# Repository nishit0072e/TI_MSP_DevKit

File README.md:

### 3D View

### Schematic View

### Front Copper

### Rear Copper

### SilkScreen

### Solder Mask

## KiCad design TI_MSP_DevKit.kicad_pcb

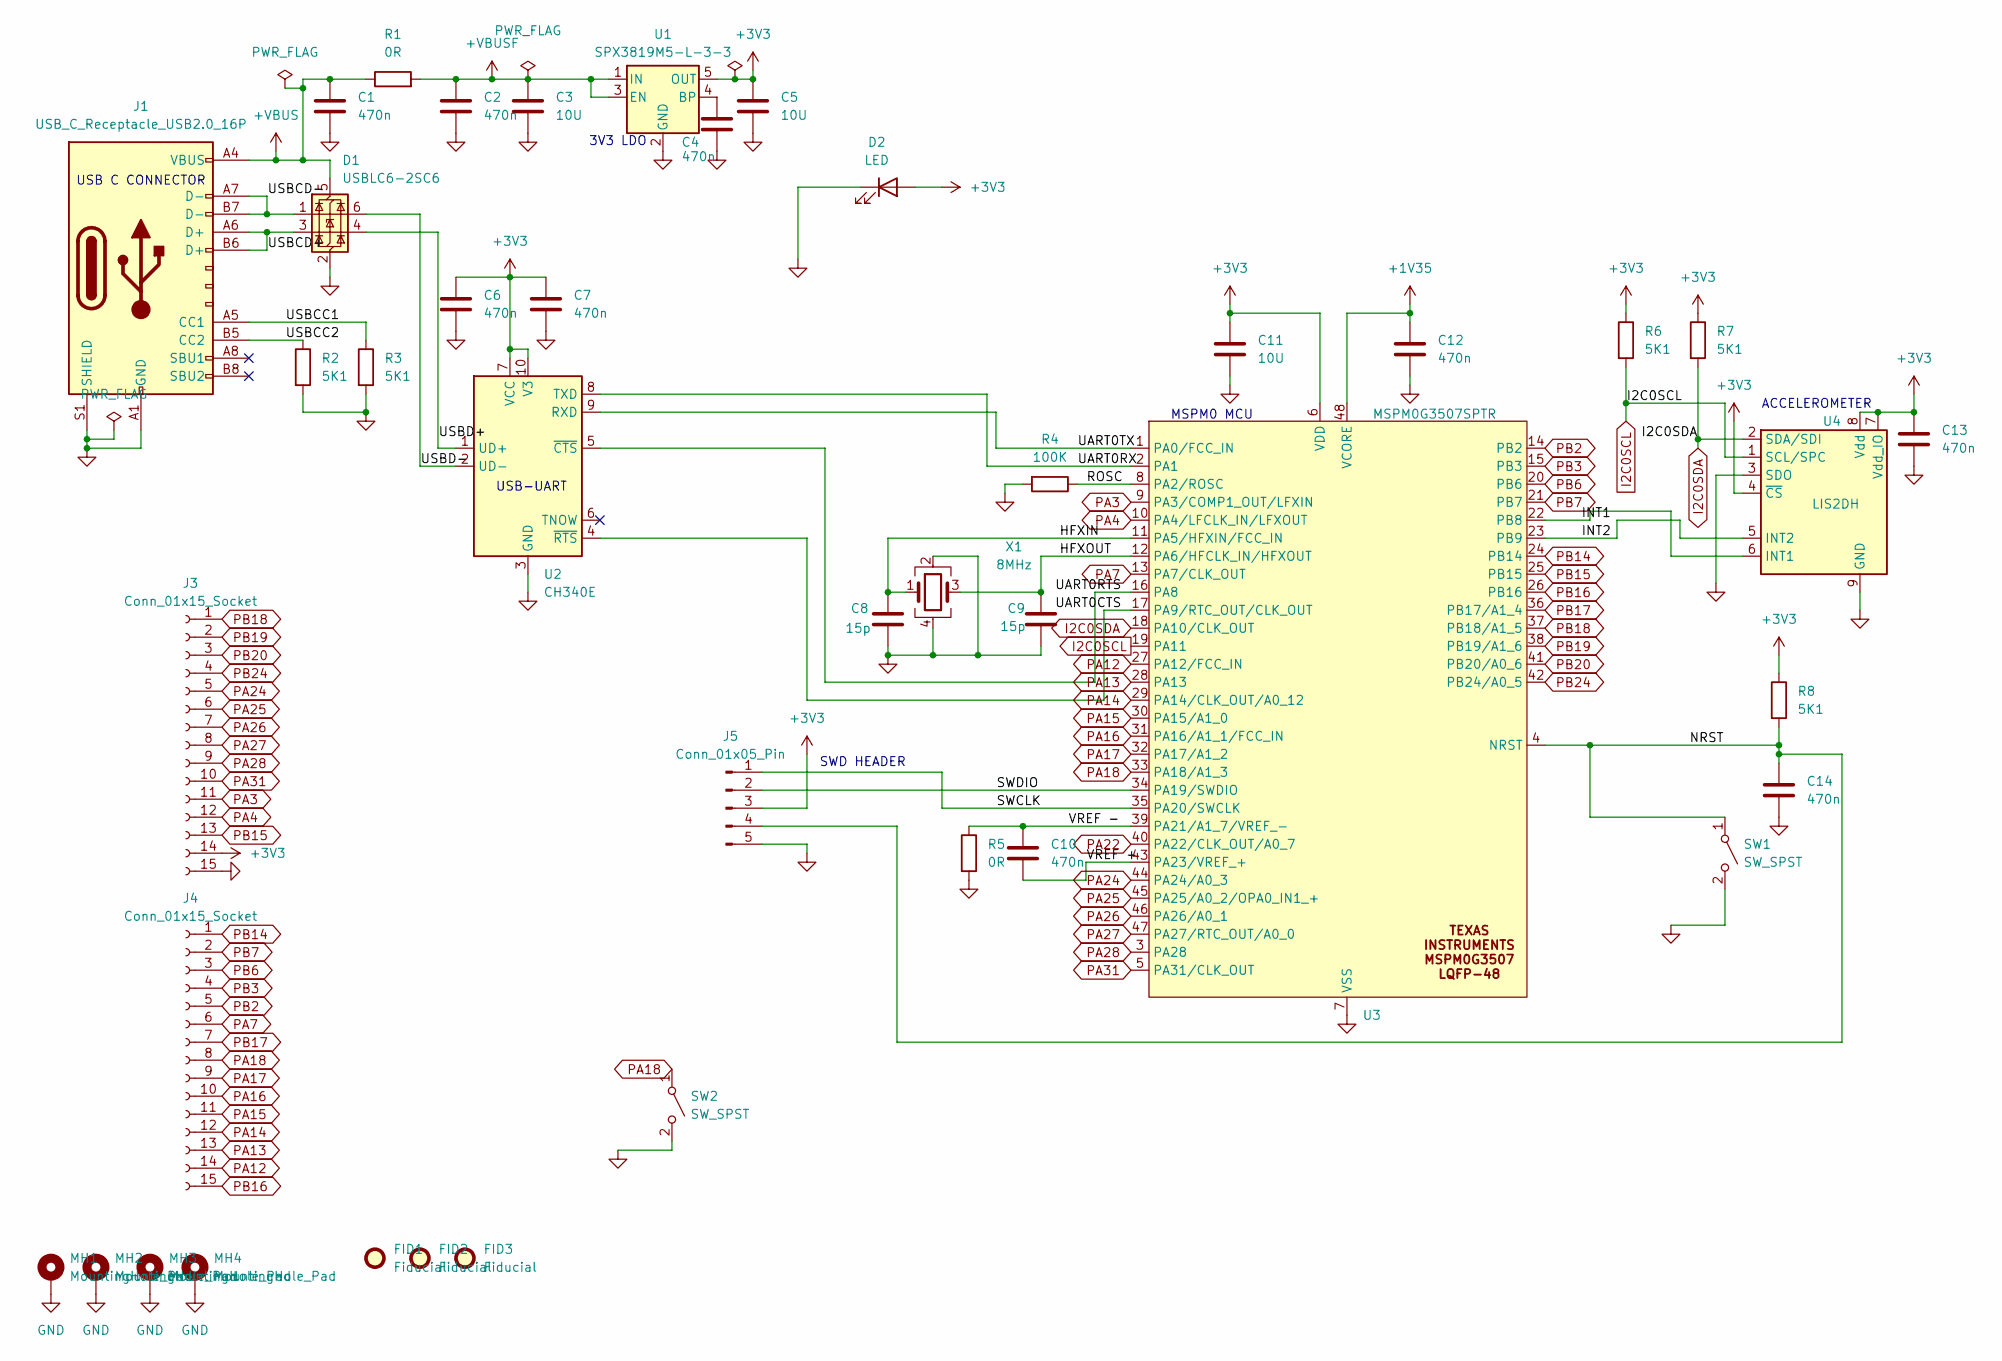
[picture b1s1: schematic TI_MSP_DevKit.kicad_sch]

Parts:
C1, C2, C4, C6, C7, C10, C12, C13, C14: 470n; C_0603_1608Metric_Pad1.08x0.95mm_HandSolder; Part Number CL21B474KBFNNNE; LCSC C13967
C3, C5, C11: 10U; C_0805_2012Metric_Pad1.18x1.45mm_HandSolder; Part Number CL21A106KAYNNNE; LCSC C15850
C8, C9: 15p; C_0603_1608Metric_Pad1.08x0.95mm_HandSolder; Part Number CL21B474KBFNNNE; LCSC C2594277
D1: USBLC6-2SC6; SOT-23-6; LCSC C2827654
D2: LED; LED_0603_1608Metric; LCSC C19171390
FID1, FID2, FID3: Fiducial; Fiducial_1mm_Mask2mm
J1: USB_C_Receptacle_USB2.0_16P; USB_C_Receptacle_GCT_USB4105-xx-A_16P_TopMnt_Horizontal; LCSC C2765186
J3, J4: Conn_01x15_Socket; PinSocket_1x15_P2.54mm_Vertical; LCSC C7499333
J5: Conn_01x05_Pin; PinSocket_1x05_P2.54mm_Vertical; LCSC C42431835
MH1, MH2, MH3, MH4: MountingHole_Pad; MountingHole_3.2mm_M3_Pad_Via
R1, R5: 0R; R_0603_1608Metric_Pad0.98x0.95mm_HandSolder; LCSC C95177
R2, R3, R6, R7, R8: 5K1; R_0603_1608Metric_Pad0.98x0.95mm_HandSolder; LCSC C2907044
R4: 100K; R_0603_1608Metric_Pad0.98x0.95mm_HandSolder; Part Number RT0603BRD07100KL; LCSC C122538
SW1, SW2: SW_SPST; SW_SPST_B3U-1000P; LCSC C720477
U1: SPX3819M5-L-3-3; SOT-23-5; LCSC C9055
U2: CH340E; MSOP-10_3x3mm_P0.5mm; LCSC C99652
U3: MSPM0G3507SPTR; LQFP-48_7x7mm_P0.5mm; Manufacturer Part Number MSPM0G3507SPTR; LCSC C22362630
U4: LIS2DH; LGA-14_2x2mm_P0.35mm_LayoutBorder3x4y; LCSC C110926
X1: 8MHz; Crystal_SMD_3225-4Pin_3.2x2.5mm_HandSoldering; LCSC C390495

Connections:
+1V35: C12.1, U3.48 (VCORE)
+3V3: C5.1, C6.1, C7.1, C11.1, C13.1, D2.2 (A), J3.14, J5.3, R6.1, R7.1, R8.1, U1.5 (OUT), U2.7 (VCC), U2.10 (V3), U3.6 (VDD), U4.4 (~CS), U4.7 (Vdd_IO), U4.8 (Vdd)
+VBUS: C1.1, D1.5 (VBUS), J1.A4 (VBUS), J1.A9 (VBUS), J1.B4 (VBUS), J1.B9 (VBUS), R1.1
+VBUSF: C2.1, C3.1, R1.2, U1.1 (IN), U1.3 (EN)
/HFXIN: C8.1, U3.11 (PA5/HFXIN/FCC_IN), X1.1
/HFXOUT: C9.1, U3.12 (PA6/HFCLK_IN/HFXOUT), X1.3
/INT1: U3.22 (PB8), U4.6 (INT1)
/INT2: U3.23 (PB9), U4.5 (INT2)
/NRST: C14.1, J5.4, R8.2, SW1.1 (A), U3.4 (NRST)
/ROSC: R4.1, U3.8 (PA2/ROSC)
/SWCLK: J5.1, U3.35 (PA20/SWCLK)
/SWDIO: J5.2, U3.34 (PA19/SWDIO)
/UART0CTS: U2.4 (~RTS), U3.17 (PA9/RTC_OUT/CLK_OUT)
/UART0RTS: U2.5 (~CTS), U3.16 (PA8)
/UART0RX: U2.8 (TXD), U3.2 (PA1)
/UART0TX: U2.9 (RXD), U3.1 (PA0/FCC_IN)
/USBCC1: J1.A5 (CC1), R3.1
/USBCC2: J1.B5 (CC2), R2.1
/USBCD+: D1.3 (I/O2), J1.A6 (D+), J1.B6 (D+)
/USBCD-: D1.1 (I/O1), J1.A7 (D-), J1.B7 (D-)
/USBD+: D1.4 (I/O2), U2.1 (UD+)
/USBD-: D1.6 (I/O1), U2.2 (UD-)
/VREF +: C10.2, U3.43 (PA23/VREF_+)
/VREF -: C10.1, R5.1, U3.39 (PA21/A1_7/VREF_-)
GND: C1.2, C2.2, C3.2, C4.2, C5.2, C6.2, C7.2, C8.2, C9.2, C11.2, C12.2, C13.2, C14.2, D1.2 (GND), D2.1 (K), J1.A1 (GND), J1.A12 (GND), J1.B1 (GND), J1.B12 (GND), J1.S1 (SHIELD), J3.15, J5.5, MH1.1, MH2.1, MH3.1, MH4.1, R2.2, R3.2, R4.2, R5.2, SW1.2 (B), SW2.2 (B), U1.2 (GND), U2.3 (GND), U3.7 (VSS), U4.3 (SDO), U4.9 (GND), X1.2, X1.4
I2C0SCL: R6.2, U3.19 (PA11), U4.1 (SCL/SPC)
I2C0SDA: R7.2, U3.18 (PA10/CLK_OUT), U4.2 (SDA/SDI)
unnamed: C4.1, U1.4 (BP)
unnamed: U4.10 (GND), U4.11 (GND), U4.12 (GND), U4.13 (GND), U4.14 (GND)
PA3: J3.11, U3.9 (PA3/COMP1_OUT/LFXIN)
PA4: J3.12, U3.10 (PA4/LFCLK_IN/LFXOUT)
PA7: J4.6, U3.13 (PA7/CLK_OUT)
PA12: J4.14, U3.27 (PA12/FCC_IN)
PA13: J4.13, U3.28 (PA13)
PA14: J4.12, U3.29 (PA14/CLK_OUT/A0_12)
PA15: J4.11, U3.30 (PA15/A1_0)
PA16: J4.10, U3.31 (PA16/A1_1/FCC_IN)
PA17: J4.9, U3.32 (PA17/A1_2)
PA18: J4.8, SW2.1 (A), U3.33 (PA18/A1_3)
PA22: U3.40 (PA22/CLK_OUT/A0_7)
PA24: J3.5, U3.44 (PA24/A0_3)
PA25: J3.6, U3.45 (PA25/A0_2/OPA0_IN1_+)
PA26: J3.7, U3.46 (PA26/A0_1)
PA27: J3.8, U3.47 (PA27/RTC_OUT/A0_0)
PA28: J3.9, U3.3 (PA28)
PA31: J3.10, U3.5 (PA31/CLK_OUT)
PB2: J4.5, U3.14 (PB2)
PB3: J4.4, U3.15 (PB3)
PB6: J4.3, U3.20 (PB6)
PB7: J4.2, U3.21 (PB7)
PB14: J4.1, U3.24 (PB14)
PB15: J3.13, U3.25 (PB15)
PB16: J4.15, U3.26 (PB16)
PB17: J4.7, U3.36 (PB17/A1_4)
PB18: J3.1, U3.37 (PB18/A1_5)
PB19: J3.2, U3.38 (PB19/A1_6)
PB20: J3.3, U3.41 (PB20/A0_6)
PB24: J3.4, U3.42 (PB24/A0_5)

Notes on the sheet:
MSPM0 MCU
ACCELEROMETER
USB-UART
SWD HEADER
USB C CONNECTOR
3V3 LDO

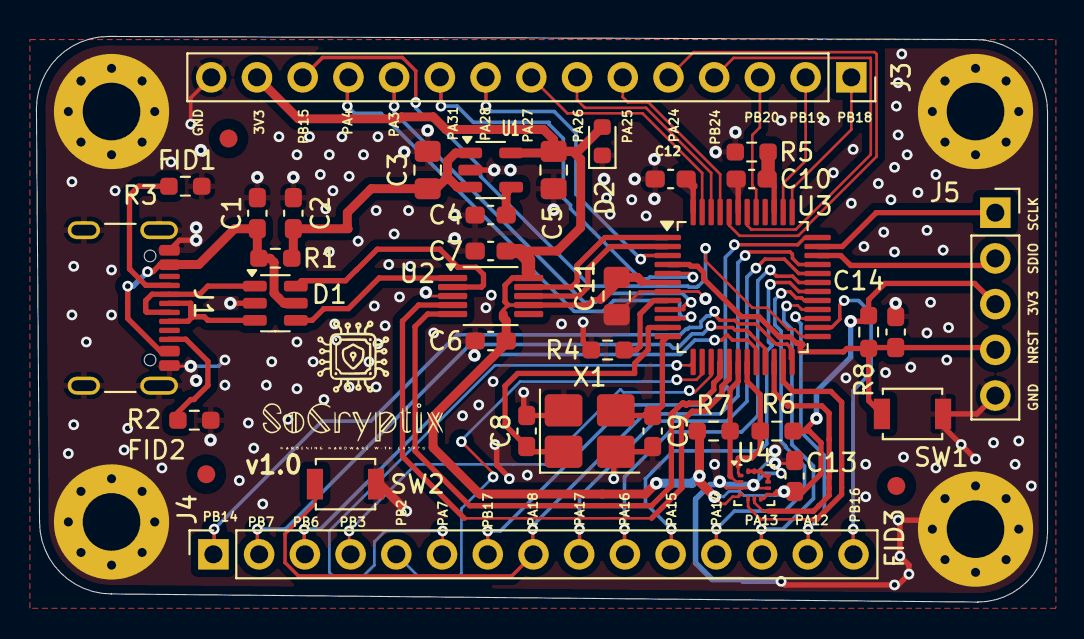
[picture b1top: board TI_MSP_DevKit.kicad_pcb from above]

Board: 2 copper layers, 56.2 x 31.4 mm, 42 parts (0 on the bottom side), 57 nets.

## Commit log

2026-05-03 image commit
2026-05-03 Update README with images of the TI MSP DevKit
    Added images for 3D view, schematic, and various copper layers.
